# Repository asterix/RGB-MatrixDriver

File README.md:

# RGB-MatrixDriver

This document describes usage of [RGB LED matrix](https://www.adafruit.com/products/420) and similar matrices.

## Introduction

The RGB LED Matrices are large scale panels which are the ones which are used on video walls (for example in Times Square or on the faces of skyscrapers). Essentially these are ordered rows of RGB LEDs with no driving logic or controllers on them what-so-ever. All driving and control logic needs to be implemented externally.

You can buy these on Adafruit or order directly from China. Note however that there is no uniformity or conformity in what is being sold out there. Each lot is different. Each manufacturer has his own set of ICs and driving mechanism (most use one of them). Beaware of this when your order. They're not very expensive. In general a ```16x32``` matrix costs about $25 in the U.S. and $10 when ordered from China.

Here is what they look like: (shown ```16x32 matrix```)
Front side:

Rear side:

## Wiring and Connectors
Depending on the panel height, the pinout may vary slightly. The pinout on the input is shown below (pictures from Adafruit)

```16 row matrix```

```32 row matrix```

The pins are listed below with their functions:
```
R1  -> Red primary row
B1  -> Blue primary row
G1  -> Green primary row
R2  -> Red multiplexed row
B2  -> Blue multiplexed row
G2  -> Green multiplexed row
A   -> First address line (MSB)
B   -> Second address line
C   -> Third address line (LSB or when D exists, D is LSB)
D   -> Fourth address line (height >= 32 only). GND when height = 16.
CLK -> Clock line used to shift bits in.
~OE -> Active low line to determine of the LEDs are ON or OFF.
LAT -> Latch line to latch-in the clocked color bits for the twin-row at once.
GND -> 3 or 4 ground pins. Connect them all to ground.
```

Below shown is a compatible wiring used in this project. You can however modify wiring to suit your needs with the exception of ``` ~OE -> GPIO18``` because this uses ```PWM``` and it is only possible on ```GPIO18```.

Tip: Since wiring and re-wiring can be a nightmare since there are 3 sets of numbers (Rasp Pi GPIO number, Rasp Pi pin number and Matrix input), you might want to create a custom populated connector like the one shown below:

If you're using a hat or another adapter, the need is obviated, but still I find this very very useful and time saving.

## Logic on the panel

On the rear side marked out are the digital logic ICs. First, ```74HC245/74HCT245``` are used to buffer inputs. Depending on which one of those your panel has, you might need to add a logic level converter from ```3.3V to 5V```.

```TTL``` logic, ```74HCT245``` can handle inputs from ```2.6V to 5V``` as logic high and this plays well (larger input noise margins) with Raspberry Pi or other ```3.3V GPIO``` output directly without any level converter.

However if you have the ```CMOS``` version, ```74HC245```, the input noise margins are pretty low so logic high is only detected from 3.5V to 5V. You most definitely need a logic level converter . You can easily build your own with 2 ```74HCT245```s for all 12 input lines. My personal favorite method is to desolder the ```74HC245``` chips and solder in the ```74HCT245``` ones. Generally these matrices have them in SO-20 package like the one you can buy from Digikey [here](http://www.digikey.com/product-detail/en/nxp-semiconductors/74HCT245D,653/568-1530-1-ND/763405). If you don't want to go through this trouble, the there is also a designed adapter available [here](./rgb-matrix-hat) which you could print and populate yourself. Adafruit also has a full hat for this. 

The other important IC on the panel is ```74HC138``` which decodes the row address (```3:8 decoder```). This is ```74HC238``` on ```32x32``` panels decoding ```4:16``` rows. Lines ```A, B, C and D (only present when height of the matrix is 32 or more)``` are decoded from binary to activate a particular twin row. Two rows separated by half the panel are addressed at once. Such a multiplexing reduces overall flicker than when consecutive lines are addressed together.

```74HC123```, which is monostable multivibrator, is used probably to reshape ```CLK or ~OE``` (I'm not sure which one it is) when forwarding to the next cascaded panel through the output connector.

The other yellow outlined ICs (```DP5020```) are just 16-bit shift registers. There are 12 of these on each ```16x32 panel```. This implies ```32 LEDs x 2 Rows x 3 Channels (R, G and B) = 192 bits``` of possible storage at any instant of time.

## Driving mechanism

Driving these panels is pretty intensive task. Each bit of each color channel has to be accurately timed to produce the desired color. This is the part I struggled to understand initially and it took me a while, so I'll try to explain this as clearly as possible.

As explained in the previous section, each address corresponds to two row separated by half the panel height. For example, if the panel is 16 rows high, then ```ABC = 000``` corresponds to row 0 and row 8 together. Let's call this a twin-row for all future references. Similarly for ```32x32``` panels ```ABCD = 0002``` corresponds to row 2 and row 18. The top (primary) row receives color data from ```R1, G1 and B1``` lines while the bottom row (multiplexed) receives data from ```R2, G2 and B2``` lines.

So for each clock cycle, 6 bits are shifted in (one of R/G/B(1) and R/G/B(2)). So to clock in a twin-row it takes width number of clock cycles. 32 clock cycles for one ```16x32``` Matrix for example. If cascaded, one twin-row corresponds to the full cascaded width. For example if you cascaded 3 panels of ```32 LED width``` each, then your twin-row will be ```96 bits``` wide hence taking ```96 clock cycles``` to shift in. Remind you that clocking a full twin-row corresponds to just one bitplane, i.e, just one bit of ```R/G/B``` of 8-bit color.

Now, how does this show the required color? This is where timing and weighting kick in. Each bitplane of color needs to be held after latching for proportional amount of time. Since each bit of a binary number has a weight of power of two, that'll be amount of time for which it is held. For example if ```bit-0``` is held for 0.125us, then ```bit-1``` is held for 0.25us, ```bit-2``` for 0.5us and so on. This needs accurate timing else hues will smudge in. Hence we use PWM.

Drive procedure:
```
Step 0: Start
Step 1: Set twin-row address on A, B, C, D
Step 2: Put a bitplane of corresponding row pixels on R1, B1, G1 and R2, B2, G2
Step 3: Drive CLK from LOW->HIGH (rising edge)
Step 4: Drive LAT from LOW->HIGH (rising edge)
Step 5: Drive ~OE LOW
Step 6: Wait for bitplane weighted time
Step 7: Drive OE HIGH
Step 8: Go back to Step 2 to output the next bitplane (until all bitplanes)
Step 9: Change A, B, C, D to select the next twin-row (until all rows)
Step 10: Go back to Step 0 and start over
```

Below is a logic analyzer capture of clocking in one twin-row for 8-bit planes (8-bit color).

Observe how different bitplanes are held for different times. The overlapping of clocking in during hold time is an optimization.

## Driver design
The organization and architecture of the developed driver is shown in the figure below. ```rgb-matrix``` acts as the launch pad for maintaining threads and wrapping internal structure.

The driver runs three threads. The main controller thread (Main-Thread), a pixel driving color pump thread (Pix-Driver) and the frame buffer maintenance thread (What-Thread). The main thread spawns the other two threads and waits until a termination is requested. It can handle user inputs or monitor an event.

To develop an application of to play with what is shown on the matrix all you need to do is fill pixels of the frame buffer in ```what::playground()```. Every ```true``` return changes the active frame buffer to the newly filled one.

## Code organization

```Frame buffer``` provides a mechanism of multi-stack buffers which can be filled in parallel when ```Pix-Driver``` is updating the matrix. Currently this is double-buffered, but can be easily extended to something bigger like a circular buffer by modifying ```FRAME_BUFS``` parameter and changing the mechanism of switching buffers.

The interface is separated as I plan to move this code to other boards very soon. Since the interface is abstracted in ```rgb_mtrx_ifc.h```, only this file needs to be changes for adaption to other hardware. All Raspberry Pi specific stuff is in ```rasp_pi_gpio``` class.

Futhermore, some helper classes are used to accomplish some tasks like parsing PPM files (```ppm_parser```) and loading and holding fonts (```glyph_loader``` and ```fontizer```).

To develop an application of to play with what is shown on the matrix all you need to do is fill pixels of the frame buffer in ```what::playground()```. Every ```true``` return changes the active frame buffer to the newly filled one. A new class can be build around this, if the driving operation is specialized and complex.

## Using this driver

Using is made pretty straightforward by exposing the full frame buffer in ```what::playground()```. Applications themselves go in the file ```matrix_appl.cpp```. Keep ```main()``` minimal as is. There is really no need to modify it unless you're doing some really one time global operation. You can build a class/abstraction around ```what``` class to accomplish your needs.

**Note: You'll need GCC version >= 4.8.2 to build this project**

**The default setting is for Raspberry Pi 2. If you're using Raspberry Pi 1, then make the below changes**
```
In rasp_pi_gpio.h comment the RASP_PI_2 flag to compile for Pi 1.
//#define RASP_PI_2        1
```

Usage:

* To compile the code simply use the already built ```Makefile```.
* You can add additional files needed to it under the ```src section```.
* Just clone this repository using ```git clone``` and type in ```"make"``` in the main directory.
* This compiles and links to an executable named ```matrix_appl```.
* To run you'll need ```sudo``` rights. So, type in ```sudo ./matrix_appl``` and you should see your matrix light up if connected correctly.

You're free to build more examples and extend this library with more features. Just open a pull request or an issue as you go on and I will take a look at them.

## Examples

Here are some bright examples on 3 cascaded ```16x32``` matrices.

Random Equalizer Bars:

Scrolling dynamic text:

## Acknowledgements

Thanks to [hzeller](https://github.com/hzeller) for his work, I had some way of verifying that my panels were ok and indeed learnt quite a bit from his code base. Some parts of this repository have been influenced by his nice ideas of driving the display. The very first time I got these panels in my hands, I ran some of his demos and was impressed by the colors on these displays. So impressed that I decided to write my own :).

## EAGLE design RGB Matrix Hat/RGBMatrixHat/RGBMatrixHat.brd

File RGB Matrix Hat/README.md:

# RGB Matrix Hat

I've designed and shared a small PCB which will let you convert Raspberry Pi's 3.3V GPIO outputs to a TTL compatible 5V levels that are needed for RGB LED matrices.
You'll need to populate this PCB with ```74HCT245``` with ```20-SOIC package``` and jumpers.

The full design is available under ```RGBMatrixHat``` directory. This is done in ```Eagle```.

The first jumper is ```J1 = 12x2``` which is minimal and snaps straight into first ```12x2 pins``` of your Raspberry Pi. The second ```J2 = 8x2``` is an IDC header.
Just solder those in and you're good to go.

## OSH Park share

Find this design shared on [OSH Park](https://oshpark.com/shared_projects/b1aH2VRL) or use the permalink ```https://oshpark.com/shared_projects/b1aH2VRL```.

Have fun!

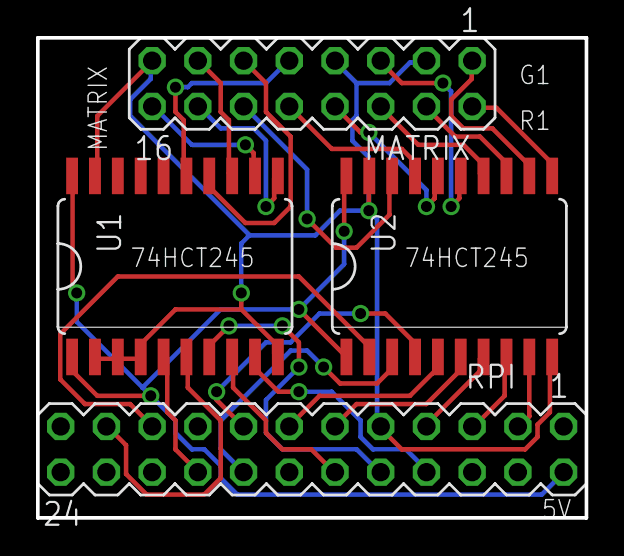
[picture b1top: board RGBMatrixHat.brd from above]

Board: 2 copper layers, 30.5 x 26.7 mm, 4 parts (0 on the bottom side), 28 nets.

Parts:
MATRIX: J2; MA08-2
RPI: J1; MA12-2
U1, U2: 74LS245DW; SO20W

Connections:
GND: MATRIX.3, MATRIX.7, MATRIX.15, RPI.9, U1.2, U1.3, U1.4, U1.10, U1.19, U2.10, U2.19
unnamed: RPI.3, U2.9
unnamed: RPI.5, U2.8
unnamed: RPI.7, U2.7
unnamed: MATRIX.2, U2.11
unnamed: MATRIX.4, U2.13
unnamed: MATRIX.5, U2.15
unnamed: MATRIX.1, U2.12
unnamed: RPI.11, U2.6
unnamed: RPI.13, U2.5
unnamed: RPI.15, U2.4
unnamed: MATRIX.6, U2.14
unnamed: MATRIX.8, U2.16
unnamed: MATRIX.14, U1.11
unnamed: RPI.8, U1.9
unnamed: MATRIX.10, U2.17
unnamed: MATRIX.12, U2.18
unnamed: MATRIX.16, U1.12
unnamed: RPI.19, U2.2
unnamed: RPI.16, U2.3
unnamed: MATRIX.9, U1.15
unnamed: MATRIX.11, U1.14
unnamed: RPI.12, U1.8
unnamed: MATRIX.13, U1.13
unnamed: RPI.10, U1.7
unnamed: RPI.2, U1.1, U1.20, U2.1, U2.20
unnamed: RPI.21, U1.6
unnamed: RPI.18, U1.5

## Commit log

2016-04-24 Init driver
2016-04-24 Start GPIO
2016-04-24 GPIO 0.3
2016-04-24 GPIO 0.4 working!
2016-04-26 Framework 1
2016-04-28 Added more structure
2016-04-28 Compiled new code
2016-04-28 Fixed all compiler errors
2016-04-28 Integrated interface
2016-04-28 Added logging
2016-04-28 test changes
2016-04-28 Basics 1.0, fixed some ifc bugs
2016-04-29 Version 1.0 * Still using delay waits, need to switch to hardware timers * Refresh rate is bad, need to speed up
2016-04-29 Few more changes
2016-04-29 Changes to thread runners
2016-04-29 Minor update
2016-04-30 Improved and merged color writes * Added interface enums
2016-04-30 More enhancements
2016-05-01 PWM on OE complete
2016-05-01 PWM OE control final
2016-05-02 Fixed datarace to access framebuffer
2016-05-02 Adjusted PMW range cycles for brighter colors
2016-05-02 CPU - RealTime Thread binding
2016-05-04 Adding PPM parser
2016-05-05 PPM parser done * Added some unicode emoticons
2016-05-07 Added heart
2016-05-07 Added BDF font parser
2016-05-07 Adding BDF Spec
2016-05-08 Adding fontizer
2016-05-08 Fixed access bug
2016-05-08 Cleaned application file
2016-05-08 Scrolling texts & fonts
2016-05-08 Update baseline info
2016-05-08 Cascaded matrices
2016-05-09 Changed emoticon color
2016-05-10 Equalizer bars
2016-05-11 Added Equalizer bars
    Cleaned up a little
2016-05-11 Turned off logging
2016-05-12 Starting documentation
2016-05-12 Adding images
2016-05-12 Wiring change
2016-05-13 Documentation 1.0
2016-05-16 More documentation
2016-05-20 Adding PCB design for RGBMatrixHat
2016-05-20 OSHPark DRC+CAM
2016-05-20 Added hat renders
2016-05-25 Compressed Eagle files
2016-06-02 Corrected Hat link
2016-06-06 Revised Hat design - Rev-2
2016-06-21 Adding soldered header photos
2016-07-01 Added compiler version comment
2016-07-08 Moving pix_driver to CORE0
    * Backward RPi 1 compatibility
